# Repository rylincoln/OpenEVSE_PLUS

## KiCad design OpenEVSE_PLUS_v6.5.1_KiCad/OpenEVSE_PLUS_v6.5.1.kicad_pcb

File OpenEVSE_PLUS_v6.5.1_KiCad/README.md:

# OpenEVSE PLUS v6.5.1 — KiCad port (2-layer)

A 1:1 port of `../OpenEVSE_PLUS_v6.5.1/OpenEVSE_PLUS_v6.5.1.sch` / `.brd` (EAGLE 9.6.2) to KiCad 10. No design changes: same parts, same nets, same copper. The EAGLE files stay as the upstream reference; new work happens here.

## How it was made

1. KiCad 10 GUI, EAGLE project import of the `.sch`/`.brd`, saved into this directory (then Update PCB from Schematic as the final step, see below). The importer embeds the EAGLE libraries as `OpenEVSE_PLUS_v6.5.1-eagle-import.kicad_sym` and `OpenEVSE_PLUS_v6.5.1-import-fps.pretty/`, both project-local.
2. `docs/research/scripts/port/sch_fix.py` on the schematic, driven by the ERC report and the EAGLE `.sch`:
   - 40 wire stubs trimmed back to their net labels and 3 EAGLE dangling stubs removed (AMP_READ, GFCI_INT, ACRELAY) — none changed a net.
   - 1 junction restored where the importer dropped an EAGLE T-connection (U1 FB onto +5V).
   - 5 no-connect flags on pins EAGLE also leaves open: D1.3, D11.3, IC4 LV, IC4 OSC, IC7 pin 5.
   - 7 PWR_FLAGs: +12V, +5V, XGND, UGND, VCC, GND, PE.
   - 8 global labels for nets EAGLE named without placing a label (the importer drops such names): XGND, -12V1, DAMP, GFI_TEST_O, DC_RELAY_1_O, DC_RELAY_1_T, DC_RELAY_2_O, DC_RELAY_2_T.
   - SH1/SH2 excluded from BOM (EAGLE attribute BOM=no).
3. `docs/research/scripts/port/pcb_fix.py` on the board, library and project:
   - SH1/SH2 (`SHORT_TOP-50`) are net ties.
   - The two bare 3.2 mm holes are H1/H2 on a board-only `MountingHole_3.2mm_NPTH`.
   - EAGLE packages that shared a name across libraries got distinct footprints: `0805_SparkFun-Capacitors` (C28, C29, C32, C33), `SOT23_transistor-npn` (Q2, Q3), `SO08_SparkFun-IC-Amplifiers` (IC1).
   - Default net class clearance 0.2 → 0.1524 mm (EAGLE's 6 mil rule for this board).

Both scripts expect the raw import as input (they are not idempotent). To rerun from a fresh import:

```bash
KICAD=/Applications/KiCad/KiCad.app/Contents/MacOS/kicad-cli
$KICAD sch erc --severity-all --format json -o erc.json OpenEVSE_PLUS_v6.5.1_KiCad/OpenEVSE_PLUS_v6.5.1.kicad_sch
python3 docs/research/scripts/port/sch_fix.py OpenEVSE_PLUS_v6.5.1_KiCad/OpenEVSE_PLUS_v6.5.1.kicad_sch erc.json OpenEVSE_PLUS_v6.5.1/OpenEVSE_PLUS_v6.5.1.sch
python3 docs/research/scripts/port/pcb_fix.py OpenEVSE_PLUS_v6.5.1_KiCad/OpenEVSE_PLUS_v6.5.1.kicad_pcb OpenEVSE_PLUS_v6.5.1_KiCad/OpenEVSE_PLUS_v6.5.1.kicad_sch OpenEVSE_PLUS_v6.5.1_KiCad/OpenEVSE_PLUS_v6.5.1-import-fps.pretty OpenEVSE_PLUS_v6.5.1_KiCad/OpenEVSE_PLUS_v6.5.1.kicad_pro
```

## Verification (kicad-cli 10.0.7)

Connectivity, compared pad for pad with `docs/research/scripts/netcmp.py`:

| comparison | differing nets |
|---|---|
| KiCad schematic netlist ↔ EAGLE `.brd` | 0 |
| KiCad schematic netlist ↔ `.kicad_pcb` | 0 |
| `.kicad_pcb` ↔ EAGLE `.brd` | 0 |

ERC: 0 errors, 42 warnings, all accepted:

- 23 `pin_to_pin` — the importer types every EAGLE `io` pin as *bidirectional*, which KiCad flags against the PWR_FLAG *power output*. Fixing pin types needs per-part datasheet work.
- 18 `endpoint_off_grid` — 0.635 mm EAGLE geometry.
- 1 `isolated_pin_label` — ADC7 label with nothing else on the net, as in EAGLE.

DRC (`--refill-zones`): 0 unconnected items, 3 errors, 230 warnings. The raw import had 8 clearance, 2 shorting-items and 7 library-mismatch violations; those are gone. What remains is in the EAGLE geometry itself:

- `starved_thermal` ×2 — Q1 pad 3 (XGND zone) and SH1 pad 2 (GND zone) get one spoke instead of KiCad's default minimum of two.
- `solder_mask_bridge` ×1 — IC2 pad 32 and L3 pad 2 are 0.153 mm apart.
- Warnings: 98 `text_height`, 62 `text_thickness` (EAGLE silk sizes), 47 `silk_over_copper`, 17 `silk_overlap`, 3 `isolated_copper` (UGND islands; EAGLE polygon had orphans=yes), 2 `silk_edge_clearance`, 1 `nonmirrored_text_on_back_layer`.

Zone fills are not stored in the files; press **B** (Refill zones) after opening the board.

## Board ↔ schematic link

The imported footprints carried no link to the schematic symbols, so the last step was **Tools → Update PCB from Schematic** in the KiCad GUI (re-link by reference designator ON, replace footprints ON, delete footprints with no symbols OFF, update fields ON). It reported 0 errors and 4 warnings (FID1–FID4 have a copper pad "1" that the fiducial symbol has no pin for; the pad has no net in EAGLE either).

`docs/research/scripts/port/pcb_geomdiff.py` compared the board before and after, matching nets by the pads they connect: 686 segments, 63 vias, 6 zones, 21 board graphics and all 117 footprint placements, pads and attributes identical. The only changes were the predicted ones:

- 30 EAGLE auto-named nets `N$…` took KiCad names `Net-(…)`.
- 21 symbol fields (PROD_ID, MPN, MF, BOM, …) were copied to footprints; I2C0, JP2 and PILOT0 got their symbol values (`M04JST-PTH-VERT`, `M06POLAR_LOCK`, `M025MM` — EAGLE deviceset names, as these parts had no value).
- The 5 open pads (D1.3, D11.3, IC4 LV/OSC, IC7.5) got `unconnected-…` nets.
- Footprints gained their sheet path links.

After the update, netcmp again reports 0 differing nets against both the EAGLE board and the schematic netlist, and DRC is unchanged (0 unconnected, the same 3 errors). `kicad-cli pcb drc --schematic-parity` still lists 22 `net_conflict` items: its parity check names nets on multi-unit symbols without the unit letter (`Net-(IC3--IN1)`), while the GUI update and `kicad-cli sch export netlist` both write `Net-(IC3A--IN1)`. Same nets, different auto-names; the GUI's own parity check does not report them.

## Known differences from the EAGLE files

- References without a trailing digit gained a `0`: AC0, FTDI0, I2C0, PILOT0, TVS0, GFCI_CT0, AMP_CT0, DC_RELAY0 (schematic and board agree).
- Parts that had no EAGLE value show their deviceset name as the value.

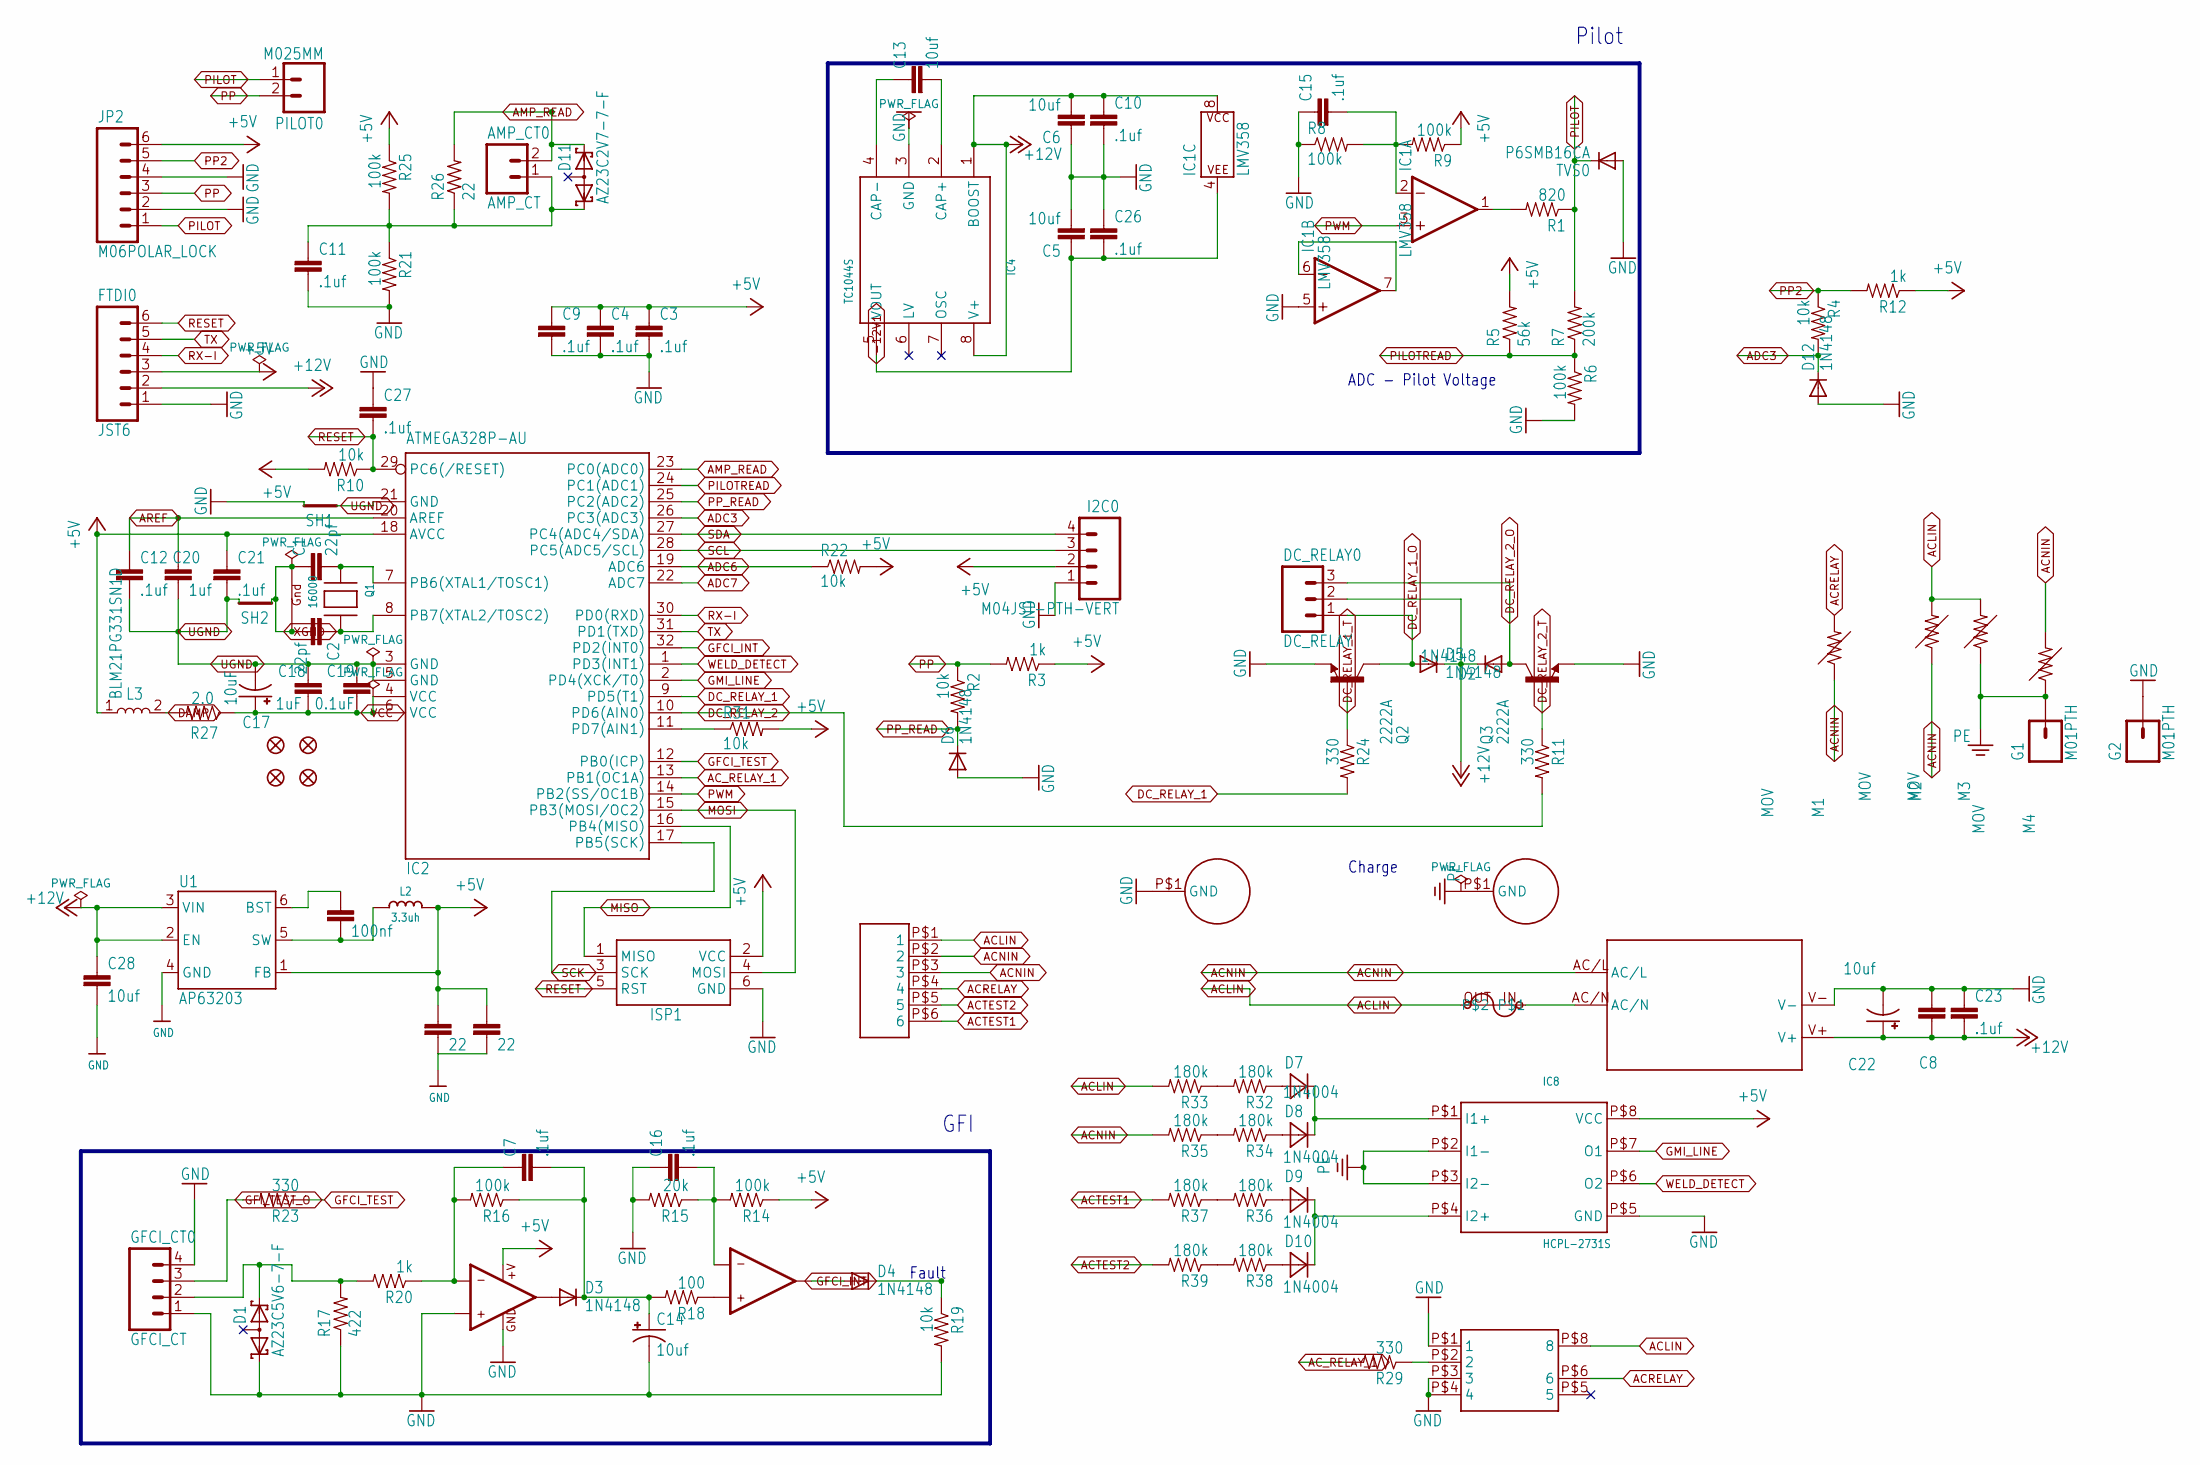
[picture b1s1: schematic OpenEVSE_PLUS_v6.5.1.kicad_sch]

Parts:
AC0: JST-VH-6
AMP_CT0: AMP_CT; MOLEX_2
C1, C2: 22pf; 0805
C3, C4, C7, C9, C10, C11, C12, C15, C16, C21, C23, C26, C27: .1uf; 0805
C5, C6, C13: 10uf; 0805
C8, C20: 1uf; 0805
C14, C22: 10uf; EIA3216
C17: 10uF; 0603-POLAR
C18: 1uF; 0805
C19: 0.1uF; 0805
C28: 10uf; 0805_SparkFun-Capacitors
C29, C33: 22; 0805_SparkFun-Capacitors
C32: 100nf; 0805_SparkFun-Capacitors
D1: AZ23C5V6-7-F; SOT23
D2, D3, D4, D5, D6, D12: 1N4148; SOD123
D7, D8, D9, D10: 1N4004; SMA
D11: AZ23C2V7-7-F; SOT23
DC_RELAY0: DC_RELAY; MOLEX_3
F1: BEL1.6AFUSE; BELFUSE1A
FID1, FID2, FID3, FID4: FIDUCIAL1X2.5; FIDUCIAL-1X2.5
FTDI0: JST6
G1, G2: M01PTH; 1X01
GFCI_CT0: GFCI_CT; GFCI_4
I2C0: M04JST-PTH-VERT; JST-4-PTH-VERT
IC1: LMV358; SO08_SparkFun-IC-Amplifiers
IC2: ATMEGA328P-AU; TQFP32-08; MPN ATMEGA8-16AU
IC3: LM358; SO08
IC4: TC1044S; SO-8
IC7: AQH2223; SIL8
IC8: HCPL-2731S; SIL8-2
ISP1: ISP1; AVRISP
JP2: M06POLAR_LOCK; MOLEX-1X6_LOCK
L2: 3.3uh; MICROBUILDER_INDUCTOR_5X5MM_NR5040_NOTHERMALS
L3: BLM21PG331SN1D; INDC2012X87
M1, M2, M3, M4: MOV
PILOT0: M025MM; SCREWTERMINAL-5MM-2
PS1: IRM-10-5
Q1: 16000; NX3225
Q2, Q3: 2222A; SOT23_transistor-npn
R1: 820; 0805
R2, R4, R10, R19, R22, R31: 10k; 0805
R3, R12, R20: 1k; 0805
R5: 56k; 0805
R6, R8, R9, R14, R16, R21, R25: 100k; 0805
R7: 200k; 0805
R11, R23, R24, R29: 330; 0805
R15: 20k; 0805
R17: 422; 0805
R18: 100; 0805
R26: 22; R1206
R27: 2.0; 0805
R32, R33, R34, R35, R36, R37, R38, R39: 180k; 1210
SH1, SH2: SHORT-HT5; SHORT_TOP-50
TVS0: P6SMB16CA; SMB
U1: AP63203; SOT23-6
U$3, U$9: HOLE

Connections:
+5V: C3.1, C4.1, C9.1, C21.1, C29.1, C33.1, FTDI0.3, I2C0.2, IC2.18 (AVCC), IC3.8 (+V), IC8.P$8 (VCC), ISP1.2 (VCC), JP2.6, L2.P$2 (2), L3.1, R3.1, R5.2, R9.1, R10.2, R12.1, R14.1, R22.2, R25.1, R31.2, U1.1 (FB)
+12V: C6.2, C8.1, C10.1, C22.A (+), C23.2, C28.1, D2.C, D5.C, DC_RELAY0.2, FTDI0.2, IC1.8 (P$V+), IC4.1 (BOOST), IC4.8 (V+), PS1.V+, U1.2 (EN), U1.3 (VIN)
-12V1: C5.1, C26.2, IC1.4 (P$V-), IC4.5 (VOUT)
ACLIN: AC0.P$1 (1), F1.OUT, IC7.P$8 (8), M2.P$2 (2), M3.P$2 (2), R33.2
ACNIN: AC0.P$2 (2), AC0.P$3 (3), M1.P$1 (1), M2.P$1 (1), M4.P$2 (2), PS1.AC/L, R35.2
ACRELAY: AC0.P$4 (4), IC7.P$6 (6), M1.P$2 (2)
ACTEST1: AC0.P$6 (6), R37.2
ACTEST2: AC0.P$5 (5), R39.2
AC_RELAY_1: IC2.13 (PB1(OC1A)), R29.2
ADC3: D12.C, IC2.26 (PC3(ADC3)), R4.2
ADC6: IC2.19 (ADC6), R22.1
ADC7: IC2.22 (ADC7)
AMP_READ: AMP_CT0.2, D11.2 (K2), IC2.23 (PC0(ADC0)), R26.2
AREF: C12.1, C20.1, IC2.20 (AREF)
DAMP: L3.2, R27.2
DC_RELAY_1: IC2.9 (PD5(T1)), R24.2
DC_RELAY_1_O: D5.A, DC_RELAY0.1, Q2.3 (C)
DC_RELAY_1_T: Q2.1 (B), R24.1
DC_RELAY_2: IC2.10 (PD6(AIN0)), R11.2
DC_RELAY_2_O: D2.A, DC_RELAY0.3, Q3.3 (C)
DC_RELAY_2_T: Q3.1 (B), R11.1
GFCI_INT: D4.C, IC2.32 (PD2(INT0)), R19.1
GFCI_TEST: IC2.12 (PB0(ICP)), R23.1
GFI_TEST_O: GFCI_CT0.3, R23.2
GMI_LINE: IC2.2 (PD4(XCK/T0)), IC8.P$7 (O1)
GND: C3.2, C4.2, C5.2, C6.1, C8.2, C9.2, C10.2, C11.2, C14.C (-), C15.1, C16.1, C22.C (-), C23.1, C26.1, C27.1, C28.2, C29.2, C33.2, D1.1 (K1), D6.A, D12.A, FTDI0.1, G2.1 (1_1), GFCI_CT0.1, GFCI_CT0.4, I2C0.1, IC1.5 (+IN), IC3.3 (+IN1), IC3.4 (GND), IC4.3 (GND), IC7.P$1 (1), IC7.P$3 (3), IC7.P$4 (4), IC8.P$5 (GND), ISP1.6 (GND), JP2.2, JP2.4, PS1.V-, Q2.2 (E), Q3.2 (E), R6.2, R8.1, R15.2, R17.1, R19.2, R21.2, SH1.2, TVS0.A, U1.4 (GND), U$9.P$1 (GND_P$1)
MISO: IC2.16 (PB4(MISO)), ISP1.1 (MISO)
MOSI: IC2.15 (PB3(MOSI/OC2)), ISP1.4 (MOSI)
unnamed: C7.2, C14.A (+), D3.C, R16.1, R18.2
unnamed: D1.2 (K2), GFCI_CT0.2, R17.2, R20.2
unnamed: D7.A, R32.1
unnamed: D8.A, R34.1
unnamed: D9.A, R36.1
unnamed: D10.A, R38.1
unnamed: AMP_CT0.1, C11.1, D11.1 (K1), R21.1, R25.2, R26.1
unnamed: F1.IN, PS1.AC/N
unnamed: C15.2, IC1.2 (-IN), R8.2, R9.2
unnamed: IC1.1 (OUT), R1.2
unnamed: IC1.6 (-IN), IC1.7 (OUT)
unnamed: C1.2, IC2.7 (PB6(XTAL1/TOSC1)), Q1.2 (X1)
unnamed: C2.1, IC2.8 (PB7(XTAL2/TOSC2)), Q1.4 (X2)
unnamed: IC2.11 (PD7(AIN1)), R31.1
unnamed: C7.1, IC3.2 (-IN1), R16.2, R20.1
unnamed: D3.A, IC3.1 (OUT1)
unnamed: IC3.5 (+IN2), R18.1
unnamed: C16.2, IC3.6 (-IN2), R14.2, R15.1
unnamed: D4.A, IC3.7 (OUT2)
unnamed: C13.2, IC4.2 (CAP+)
unnamed: C13.1, IC4.4 (CAP-)
unnamed: IC7.P$2 (2), R29.1
unnamed: D7.C, D8.C, IC8.P$1 (I1+)
unnamed: D9.C, D10.C, IC8.P$4 (I2+)
unnamed: C32.2, L2.P$1 (1), U1.5 (SW)
unnamed: R32.2, R33.1
unnamed: R34.2, R35.1
unnamed: R36.2, R37.1
unnamed: R38.2, R39.1
unnamed: C32.1, U1.6 (BST)
PE: G1.1 (1_1), IC8.P$2 (I1-), IC8.P$3 (I2-), M3.P$1 (1), M4.P$1 (1), U$3.P$1 (GND_P$1)
PILOT: JP2.1, PILOT0.1, R1.1, R7.2, TVS0.C
PILOTREAD: IC2.24 (PC1(ADC1)), R5.1, R6.1, R7.1
PP: JP2.3, PILOT0.2, R2.1, R3.2
PP2: JP2.5, R4.1, R12.2
PP_READ: D6.C, IC2.25 (PC2(ADC2)), R2.2
PWM: IC1.3 (+IN), IC2.14 (PB2(SS/OC1B))
RESET: C27.2, FTDI0.6, IC2.29 (PC6(/RESET)), ISP1.5 (RST), R10.1
RX-I: FTDI0.4, IC2.30 (PD0(RXD))
SCK: IC2.17 (PB5(SCK)), ISP1.3 (SCK)
SCL: I2C0.3, IC2.28 (PC5(ADC5/SCL))
SDA: I2C0.4, IC2.27 (PC4(ADC4/SDA))
TX: FTDI0.5, IC2.31 (PD1(TXD))
UGND: C12.2, C17.-, C18.1, C19.1, C20.2, C21.2, IC2.3 (GND), IC2.5 (GND), IC2.21 (GND), SH1.1, SH2.2
VCC: C17.+, C18.2, C19.2, IC2.4 (VCC), IC2.6 (VCC), R27.1
WELD_DETECT: IC2.1 (PD3(INT1)), IC8.P$6 (O2)
XGND: C1.1, C2.2, Q1.1 (G1), Q1.3 (G2), SH2.1

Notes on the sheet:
ADC - Pilot Voltage
Pilot
Fault
GFI
Charge

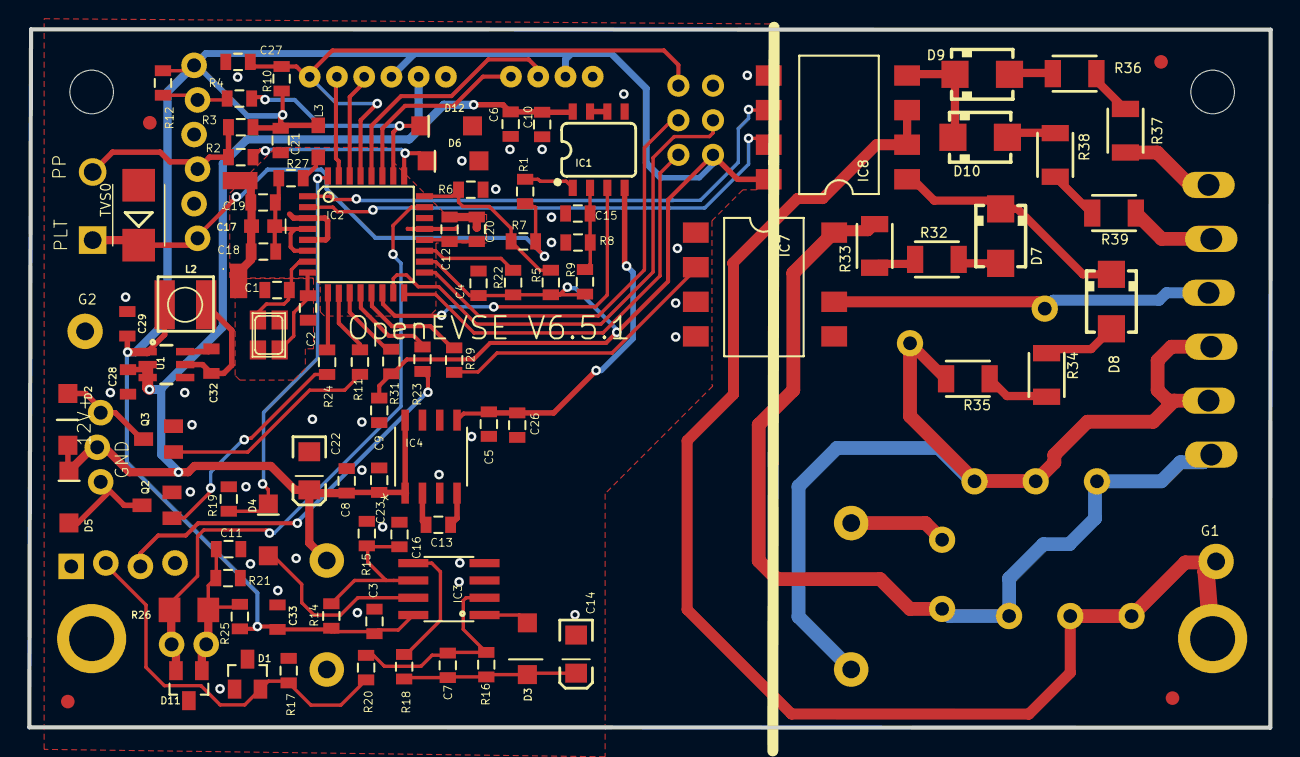
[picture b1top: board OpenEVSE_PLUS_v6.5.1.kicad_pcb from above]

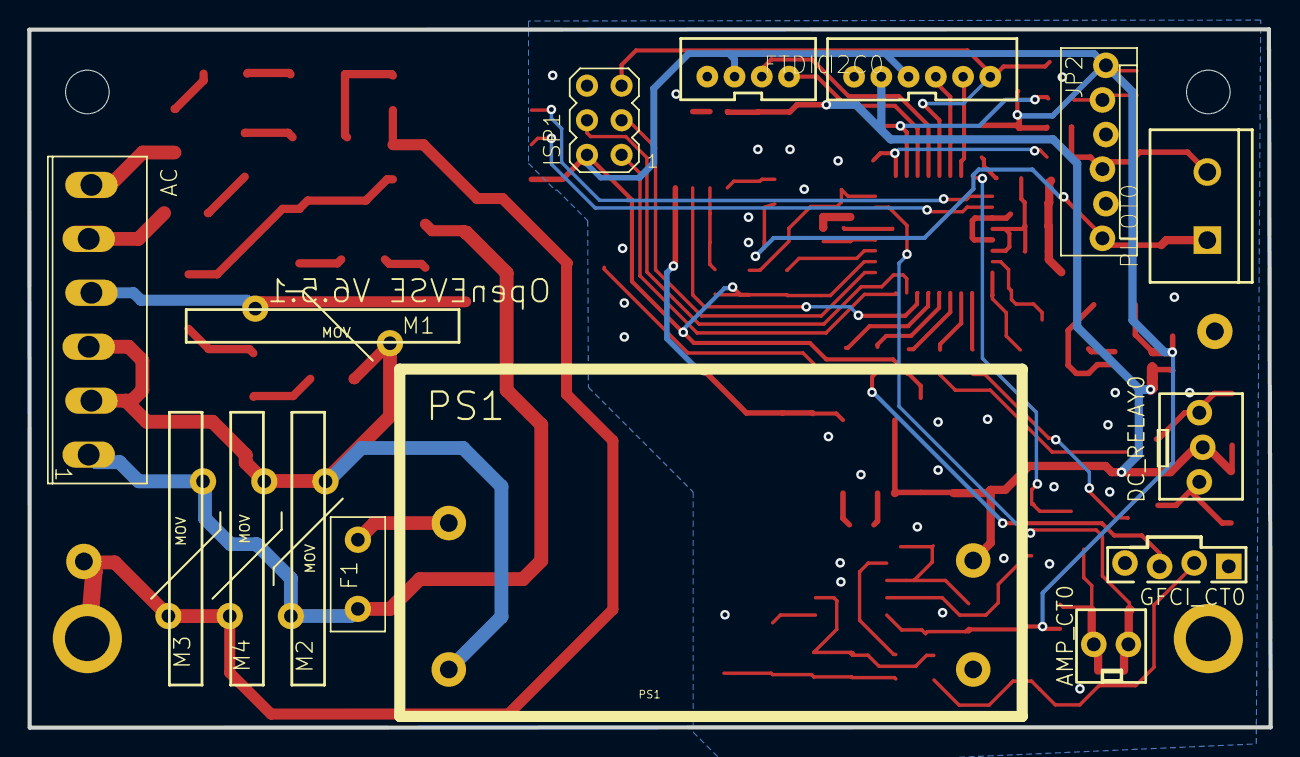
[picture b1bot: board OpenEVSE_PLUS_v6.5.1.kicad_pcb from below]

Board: 2 copper layers, 91.1 x 51.3 mm, 117 parts (15 on the bottom side), 74 nets.

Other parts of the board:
H1, H2: MountingHole_3.2mm_NPTH

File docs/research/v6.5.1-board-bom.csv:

qty,value,package,mount,eagle_device,refs,attributes
1,JST-VH-6,JST-VH-6,THT,OpenEVSE/JST-VH-6,AC,
1,AMP_CT,MOLEX_2,THT,OpenEVSE/MOLEX_2,AMP_CT,
2,22pf,0805,SMD,SparkFun/CAP0805,C1 C2,
13,.1uf,0805,SMD,SparkFun/CAP0805,C3 C4 C7 C9 C10 C11 C12 C15 C16 C21 C23 C26 C27,
4,10uf,0805,SMD,SparkFun/CAP0805,C5 C6 C13 C28,
2,1uf,0805,SMD,SparkFun/CAP0805,C8 C20,
2,10uf,EIA3216,SMD,SparkFun/CAP_POL1206,C14 C22,
1,10uF,0603-POLAR,SMD,SparkFun-Capacitors/10UF-POLAR-0603-6.3V-20%(TANT),C17,PROD_ID=CAP-13210; VALUE=10uF
1,1uF,0805,SMD,SparkFun/CAP0805,C18,
1,0.1uF,0805,SMD,SparkFun/CAP0805,C19,
2,22,0805,SMD,SparkFun-Capacitors/1.0UF-0805-25V-(+80/-20%),C29 C33,PROD_ID=CAP-11625; VALUE=1.0uF
1,100nf,0805,SMD,SparkFun-Capacitors/1.0UF-0805-25V-(+80/-20%),C32,PROD_ID=CAP-11625; VALUE=1.0uF
1,AZ23C5V6-7-F,SOT23,SMD,diode/BAS40-06,D1,
6,1N4148,SOD123,SMD,diode/DIODE-SOD123,D2 D3 D4 D5 D6 D12,
4,1N4004,SMA,SMD,diode/MBRA340T3,D7 D8 D9 D10,
1,AZ23C2V7-7-F,SOT23,SMD,diode/BAS40-06,D11,
1,DC_RELAY,MOLEX_3,THT,OpenEVSE/MOLEX_3,DC_RELAY,
1,BEL1.6AFUSE,BELFUSE1A,THT,Qxd/BEL1AFUSE,F1,
4,FIDUCIAL,FIDUCIAL-1X2.5,SMD,SparkFun-Retired/FIDUCIAL1X2.5,FID1 FID2 FID3 FID4,
1,JST6,JST6,THT,OpenEVSE/JST6,FTDI,
2,M01,1X01,THT,SparkFun/M01PTH,G1 G2,
1,GFCI_CT,GFCI_4,THT,OpenEVSE/GFCI_4,GFCI_CT,
1,LMV358,SO08,SMD,SparkFun-IC-Amplifiers/LMV358SOIC,IC1,PROD_ID=IC-09657; VALUE=LMV358
1,ATMEGA328P-AU,TQFP32-08,SMD,atmel/MEGA8-AI,IC2,MPN=ATMEGA8-16AU; OC_FARNELL=9171371; OC_NEWARK=73M8863
1,M04,JST-4-PTH-VERT,THT,SparkFun-Connectors/M04JST-PTH-VERT,I2C,
1,LM358,SO08,SMD,SparkFun/LMV358,IC3,
1,TC1044S,SO-8,SMD,OpenEVSE/TC1044S,IC4,
1,AQH2223,SIL8,SMD,OpenEVSE/AQH2223,IC7,
1,HCPL-2731S,SIL8-2,SMD,OpenEVSE/HCPL-2731S,IC8,
1,ISP1,AVRISP,THT,adafruit/AVRISP-6,ISP1,
1,M06,MOLEX-1X6_LOCK,THT,SparkFun-Connectors/M06POLAR_LOCK,JP2,
1,3.3uh,MICROBUILDER_INDUCTOR_5X5MM_NR5040_NOTHERMALS,SMD,ESP32_v1_SMPS/MICROBUILDER_INDUCTORNR5040,L2,
1,BLM21PG331SN1D,INDC2012X87,SMD,BLM21PG331SN1D/BLM21PG331SN1D,L3,DESCRIPTION= Ferrite Beads Multi-Layer 330Ohm 25% 100MHz 1.5A 70mOhm DCR 0805 Paper T/R ; MF=Murata; MP=BLM21PG331SN1D; PACKAGE=0805 Murata
4,MOV,MOV,THT,OpenEVSE/MOV,M1 M2 M3 M4,
1,M02,SCREWTERMINAL-5MM-2,THT,SparkFun-Connectors/M025MM,PILOT,STOREFRONT_ID=PRT-08432
1,IRM-10-5,IRM-10-5,THT,OpenEVSE/IRM-10-5,PS1,
1,16000,NX3225,SMD,adafruit/XTAL-4-3225,Q1,
2,2222A,SOT23,SMD,transistor-npn/BCX70*SMD,Q2 Q3,
1,820,0805,SMD,SparkFun/RESISTOR0805-RES,R1,
6,10k,0805,SMD,SparkFun/RESISTOR0805-RES,R2 R4 R10 R19 R22 R31,
3,1k,0805,SMD,SparkFun/RESISTOR0805-RES,R3 R12 R20,
1,56k,0805,SMD,SparkFun/RESISTOR0805-RES,R5,
7,100k,0805,SMD,SparkFun/RESISTOR0805-RES,R6 R8 R9 R14 R16 R21 R25,
1,200k,0805,SMD,SparkFun/RESISTOR0805-RES,R7,
4,330,0805,SMD,SparkFun/RESISTOR0805-RES,R11 R23 R24 R29,
1,20k,0805,SMD,SparkFun/RESISTOR0805-RES,R15,
1,422,0805,SMD,SparkFun/RESISTOR0805-RES,R17,
1,100,0805,SMD,SparkFun/RESISTOR0805-RES,R18,
1,22,R1206,SMD,rcl/R-US_R1206,R26,
1,2.0,0805,SMD,SparkFun/RESISTOR0805-RES,R27,
8,180k,1210,SMD,SparkFun-Resistors/0.1OHM-1/2W-1%(1210),R32 R33 R34 R35 R36 R37 R38 R39,PROD_ID=RES-12374
2,SHORT-H,SHORT_TOP-50,SMD,shorts-old/SHORT-HT5,SH1 SH2,BOM=no
1,P6SMB16CA,SMB,SMD,diode/DIODE-SMB,TVS,
1,AP63203,SOT23-6,SMD,SparkFun-IC-Power/AP63203,U1,PROD_ID=VREG-15244; VALUE=AP63203
2,HOLE,HOLE,THT,OpenEVSE/HOLE,U$3 U$9,
